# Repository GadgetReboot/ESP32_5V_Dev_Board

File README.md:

# ESP32_5V_Dev_Board
<br><br><BR><BR>
ESP32 dev board with on board 3.3v to 5v buffers to some external pins, PT8211 I2S DAC, and Micro SD Card Socket

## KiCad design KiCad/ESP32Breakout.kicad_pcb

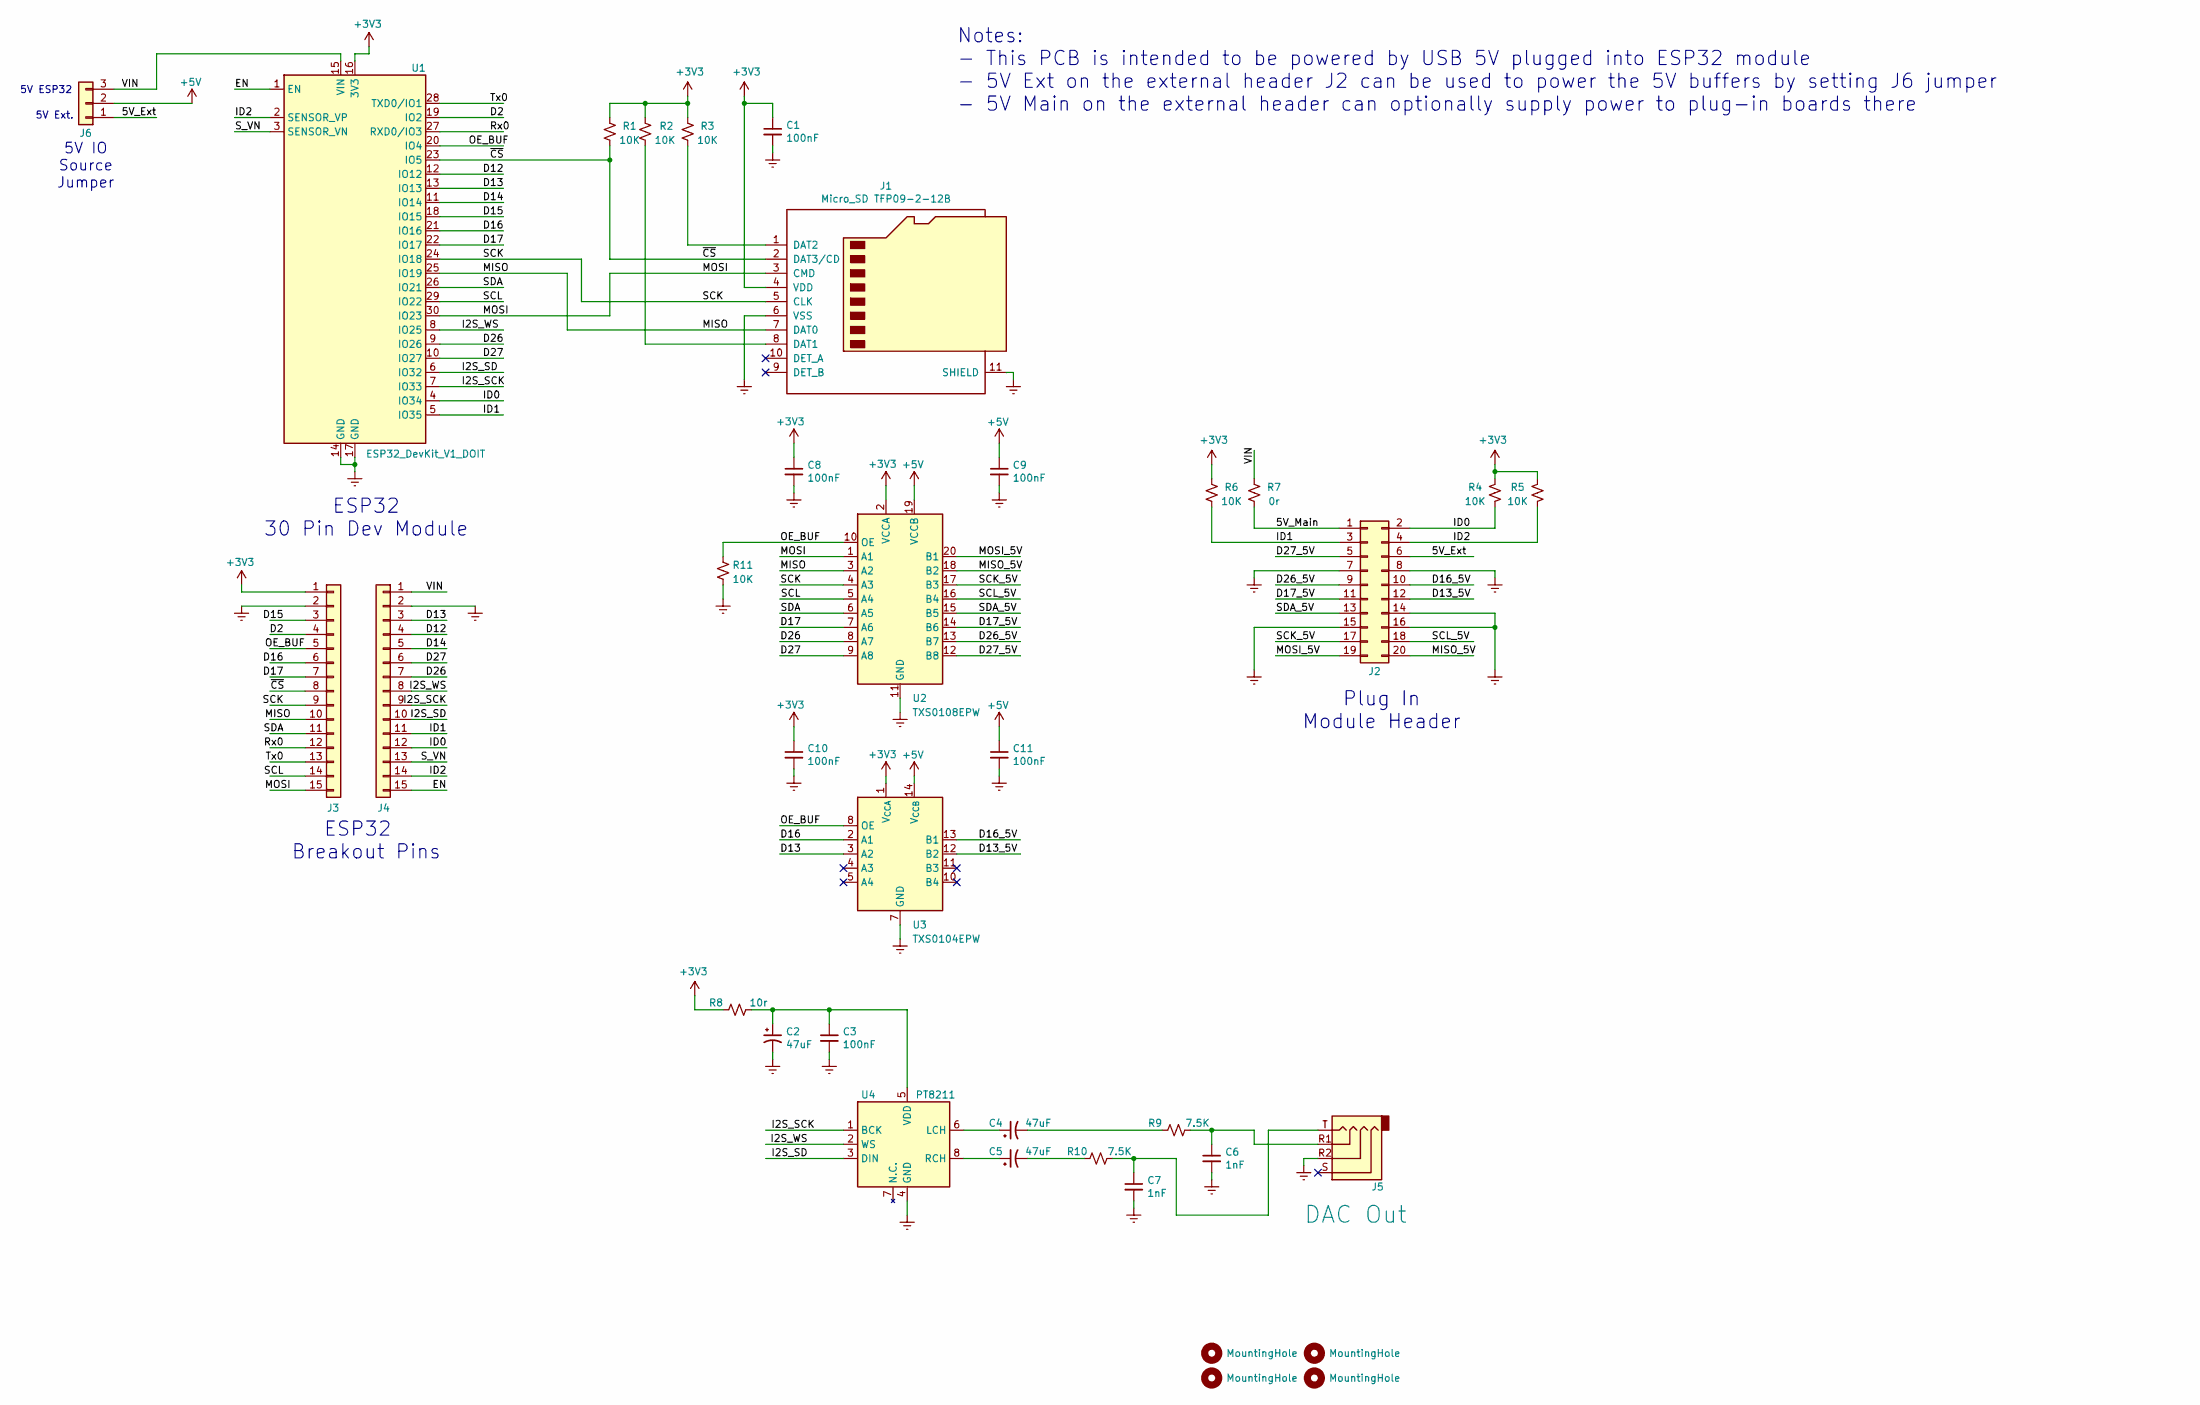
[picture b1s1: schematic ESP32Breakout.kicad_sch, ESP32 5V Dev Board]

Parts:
C1, C3, C8, C9, C10, C11: 100nF; C_0805_2012Metric_Pad1.18x1.45mm_HandSolder
C2, C4, C5: 47uF; C_Elec_4x5.4
C6, C7: 1nF; C_0805_2012Metric_Pad1.18x1.45mm_HandSolder
H1, H2, H3, H4: MountingHole; MountingHole_3.5mm
J1: Micro_SD TFP09-2-12B; TFP09212B
J2: Conn_02x10_Odd_Even; PinSocket_2x10_P2.54mm_Horizontal
J3, J4: Conn_01x15; PinHeader_1x15_P2.54mm_Vertical
J5: DAC Out; PJ320A
J6: Conn_01x03; PinHeader_1x03_P2.54mm_Vertical
R1, R2, R3, R4, R5, R6, R11: 10K; R_0805_2012Metric_Pad1.20x1.40mm_HandSolder
R7: 0r; R_0805_2012Metric_Pad1.20x1.40mm_HandSolder
R8: 10r; R_0805_2012Metric_Pad1.20x1.40mm_HandSolder
R9, R10: 7.5K; R_0805_2012Metric_Pad1.20x1.40mm_HandSolder
U1: ESP32_DevKit_V1_DOIT; esp32_devkit_v1_doit
U2: TXS0108EPW; TSSOP-20_4.4x6.5mm_P0.65mm
U3: TXS0104EPW; TSSOP-14_4.4x5mm_P0.65mm
U4: PT8211; SOIC-8_3.9x4.9mm_P1.27mm

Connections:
+3V3: C1.1, C8.1, C10.1, J1.4 (VDD), J3.1, R1.1, R2.1, R3.1, R4.1, R5.1, R6.1, R8.2, U1.16 (3V3), U2.2 (VCCA), U3.1 (V_{CCA})
+5V: C9.1, C11.1, J6.2, U2.19 (VCCB), U3.14 (V_{CCB})
/5V_Ext: J2.6, J6.1
/5V_Main: J2.1, R7.2
/D2: J3.4, U1.19 (IO2)
/D12: J4.4, U1.12 (IO12)
/D13: J4.3, U1.13 (IO13), U3.3 (A2)
/D13_5V: J2.12, U3.12 (B2)
/D14: J4.5, U1.11 (IO14)
/D15: J3.3, U1.18 (IO15)
/D16: J3.6, U1.21 (IO16), U3.2 (A1)
/D16_5V: J2.10, U3.13 (B1)
/D17: J3.7, U1.22 (IO17), U2.7 (A6)
/D17_5V: J2.11, U2.14 (B6)
/D26: J4.7, U1.9 (IO26), U2.8 (A7)
/D26_5V: J2.9, U2.13 (B7)
/D27: J4.6, U1.10 (IO27), U2.9 (A8)
/D27_5V: J2.5, U2.12 (B8)
/EN: J4.15, U1.1 (EN)
/I2S_SCK: J4.9, U1.7 (IO33), U4.1 (BCK)
/I2S_SD: J4.10, U1.6 (IO32), U4.3 (DIN)
/I2S_WS: J4.8, U1.8 (IO25), U4.2 (WS)
/ID0: J2.2, J4.12, R4.2, U1.4 (IO34)
/ID1: J2.3, J4.11, R6.2, U1.5 (IO35)
/ID2: J2.4, J4.14, R5.2, U1.2 (SENSOR_VP)
/MISO: J1.7 (DAT0), J3.10, U1.25 (IO19), U2.3 (A2)
/MISO_5V: J2.20, U2.18 (B2)
/MOSI: J1.3 (CMD), J3.15, U1.30 (IO23), U2.1 (A1)
/MOSI_5V: J2.19, U2.20 (B1)
/OE_BUF: J3.5, R11.1, U1.20 (IO4), U2.10 (OE), U3.8 (OE)
/Rx0: J3.12, U1.27 (RXD0/IO3)
/SCK: J1.5 (CLK), J3.9, U1.24 (IO18), U2.4 (A3)
/SCK_5V: J2.17, U2.17 (B3)
/SCL: J3.14, U1.29 (IO22), U2.5 (A4)
/SCL_5V: J2.18, U2.16 (B4)
/SDA: J3.11, U1.26 (IO21), U2.6 (A5)
/SDA_5V: J2.13, U2.15 (B5)
/S_VN: J4.13, U1.3 (SENSOR_VN)
/Tx0: J3.13, U1.28 (TXD0/IO1)
/VIN: J4.1, J6.3, R7.1, U1.15 (VIN)
/~CS: J1.2 (DAT3/CD), J3.8, R1.2, U1.23 (IO5)
GNDREF: C1.2, C2.2, C3.2, C6.2, C7.2, C8.2, C9.2, C10.2, C11.2, J1.6 (VSS), J1.11 (SHIELD), J2.7, J2.8, J2.14, J2.15, J2.16, J3.2, J4.2, J5.R2, R11.2, U1.14 (GND), U1.17 (GND), U2.11 (GND), U3.7 (GND), U4.4 (GND)
unnamed: C4.2, R9.2
unnamed: C5.2, R10.2
unnamed: C6.1, J5.R1, R9.1
unnamed: C7.1, J5.T, R10.1
unnamed: J1.8 (DAT1), R2.2
unnamed: J1.1 (DAT2), R3.2
unnamed: C4.1, U4.6 (LCH)
unnamed: C5.1, U4.8 (RCH)
unnamed: C2.1, C3.1, R8.1, U4.5 (VDD)

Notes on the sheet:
5V ESP32
5V Ext.
ESP32 Breakout Pins
Notes: - This PCB is intended to be powered by USB 5V plugged into ESP32 module - 5V Ext on the external header J2 can be used to power the 5V buffers by setting J6 jumper - 5V Main on the external header can optionally supply power to plug-in boards there
5V IO Source Jumper
Plug In Module Header
ESP32 30 Pin Dev Module

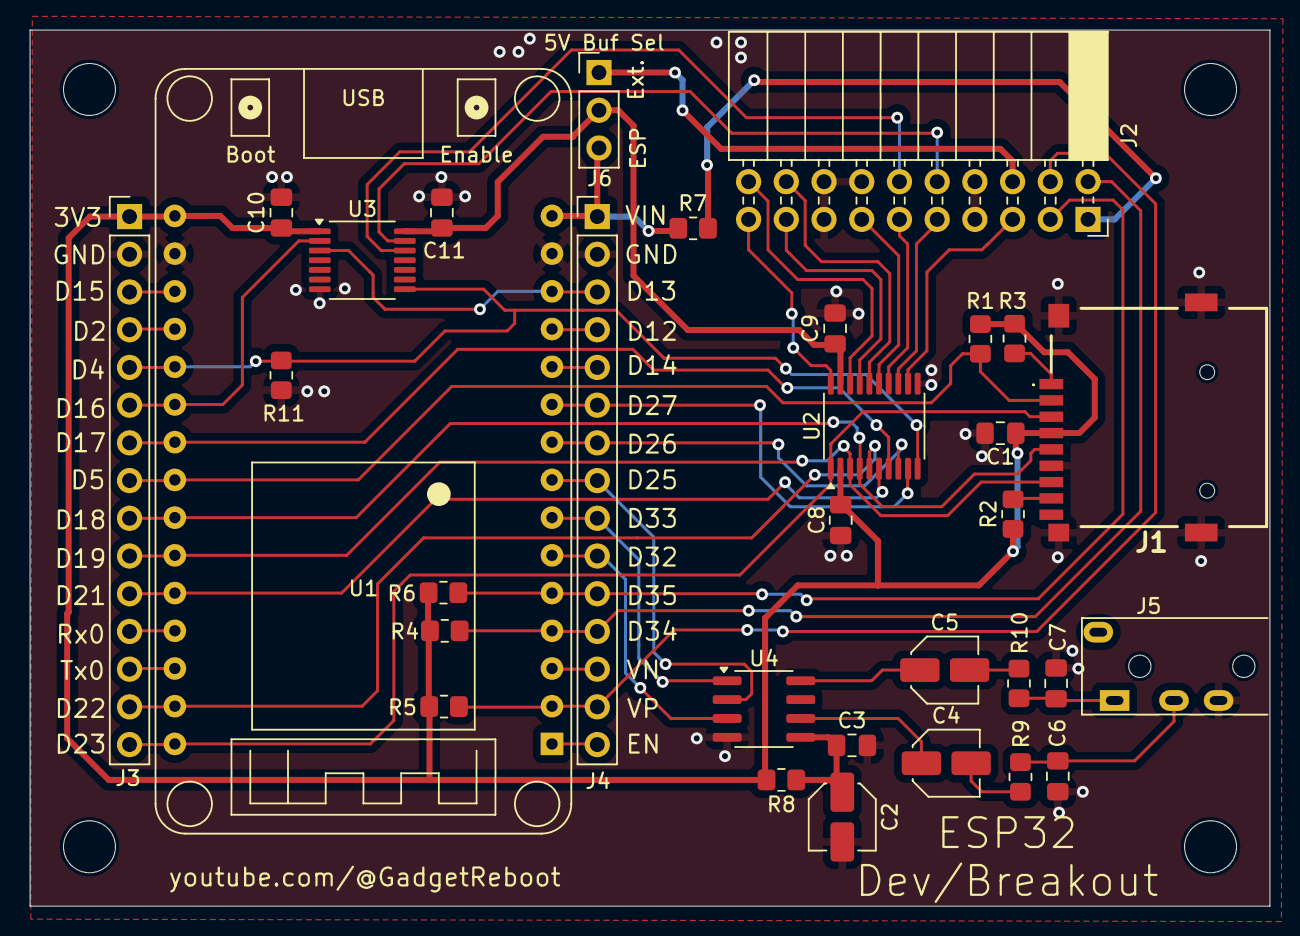
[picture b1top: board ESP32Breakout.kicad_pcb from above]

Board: 2 copper layers, 83.5 x 59.0 mm, 36 parts (0 on the bottom side), 51 nets.
